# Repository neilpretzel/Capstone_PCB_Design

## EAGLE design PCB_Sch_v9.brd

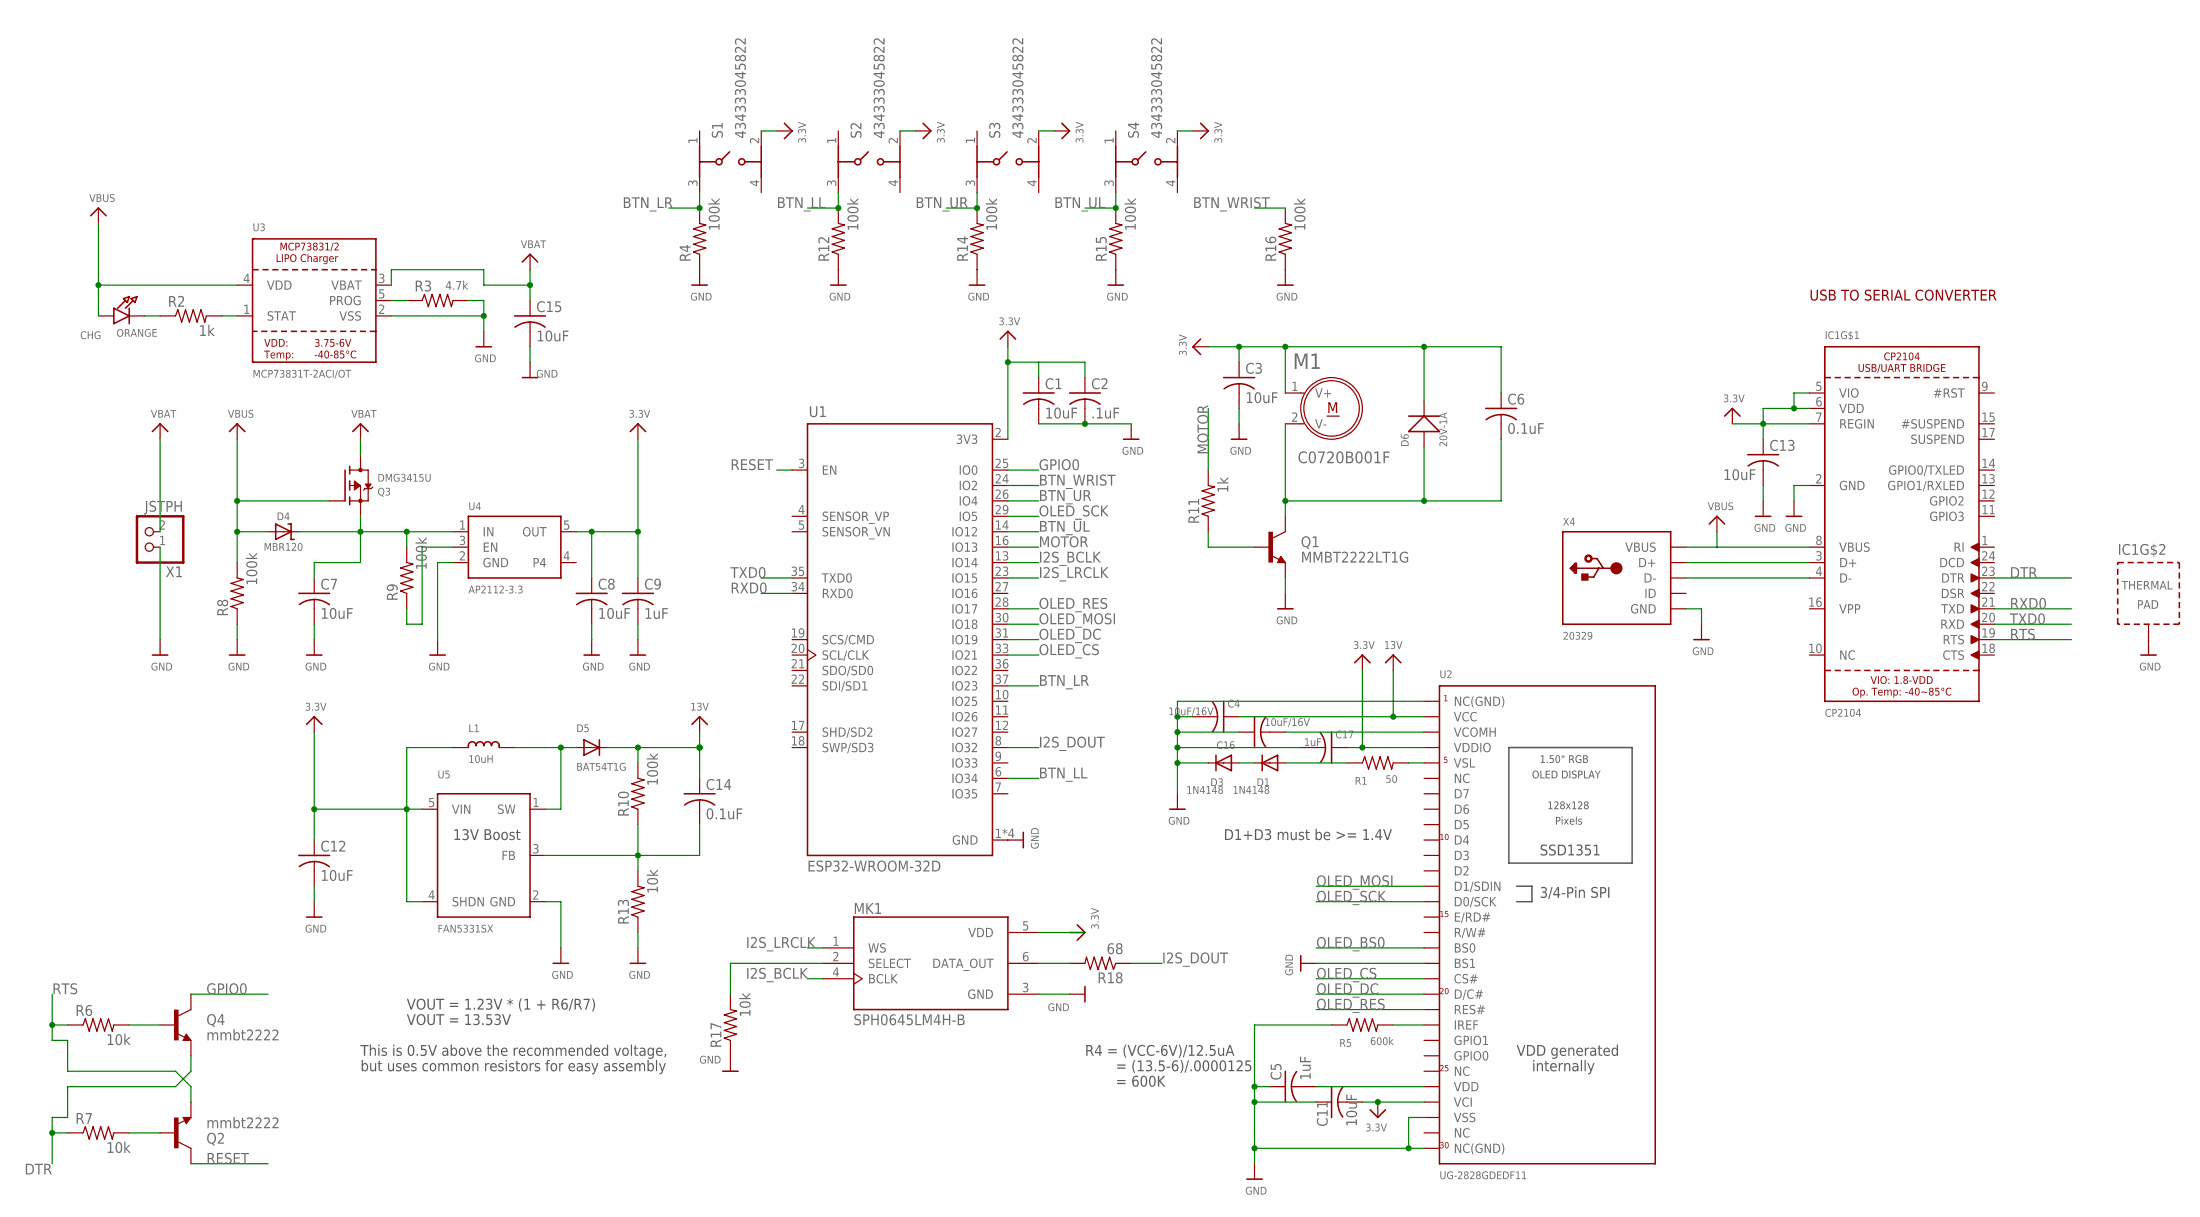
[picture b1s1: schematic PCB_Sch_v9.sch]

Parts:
C1, C3, C7, C8, C11, C12, C13, C15: 10uF; C0603
C2: .1uF; C0603
C4, C16: 10uF/16V; C0603
C5, C9, C17: 1uF; C0603
C6, C14: 0.1uF; C0603
CHG: ORANGE; CHIPLED_0805_NOOUTLINE
D1, D3: 1N4148; SOD-323
D4: MBR120; SOD-123
D5: BAT54T1G; SOD-123
D6: 20V-1A; SOD-123
IC1: CP2104; QFN24_4MM_SMSC
L1: 10uH; INDUCTOR_1007
M1: C0720B001F; XDCR_C0720B001F
MK1: SPH0645LM4H-B; MIC_SPH0645LM4H-B
Q1: MMBT2222LT1G; SOT95P237X111-3N
Q2, Q4: mmbt2222; SOT23-3
Q3: DMG3415U; SOT23-R
R1: 50; R0603
R2, R11: 1k; R0603
R3: 4.7k; R0603
R4, R8, R9, R10, R12, R14, R15, R16: 100k; R0603
R5: 600k; R0603
R6, R7, R13, R17: 10k; R0603
R18: 68; R0603
S1, S2, S3, S4: 434333045822
U1: ESP32-WROOM-32D; MODULE_ESP32-WROOM-32D
U2: UG-2828GDEDF11; FPC_XF2M-3015-1A
U3: MCP73831T-2ACI/OT; SOT23-5
U4: AP2112-3.3; SOT23-5
U5: FAN5331SX; SOT23-5@1
X1: JSTPH; JSTPH2
X4: 20329; 4UCONN_20329_V2

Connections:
3.3V: C1.1, C2.1, C3.1, C6.1, C8.1, C9.1, C11.2, C12.1, C13.1, C17.1, D6.-, IC1.5 (VIO), IC1.6 (VDD), IC1.7 (REGIN), L1.P$1 (1), M1.1 (V+), S1.2 (4), S2.2 (4), S3.2 (4), S4.2 (4), U1.2 (3V3), U2.P$4 (VCI), U2.P$27 (VDDIO), U4.5 (OUT), U5.4 (SHDN), U5.5 (VIN)
13V: C4.1, C14.1, D5.C, R10.2, U2.P$29 (VCC)
BTN_LL: R12.2, S2.3 (1), U1.6 (IO34)
BTN_LR: R4.2, S1.3 (1), U1.37 (IO23)
BTN_UL: R15.2, S4.3 (1), U1.14 (IO12)
BTN_UR: R14.2, S3.3 (1), U1.26 (IO4)
BTN_WRIST: R16.2, U1.24 (IO2)
DTR: IC1.23 (DTR), Q4.2 (E), R7.1
GND: C1.2, C2.2, C3.2, C4.2, C5.1, C7.2, C8.2, C9.2, C11.1, C12.2, C13.2, C15.2, C16.1, C17.2, D3.C, IC1.2 (GND), IC1.THERM (TP), MK1.3 (GND), Q1.2 (E), R3.2, R4.1, R5.1, R8.1, R12.1, R13.1, R14.1, R15.1, R16.1, R17.1, U1.1 (GND), U1.15 (GND), U1.38 (GND), U1.39 (GND), U2.P$1 (NC(GND)), U2.P$3 (VSS), U2.P$13 (BS1), U2.P$30 (NC(GND)), U3.2 (VSS), U4.2 (GND), U5.2 (GND), X1.1, X4.BASE@1 (GND), X4.BASE@2 (GND), X4.GND, X4.SPRT@1 (GND), X4.SPRT@2 (GND), X4.SPRT@3 (GND), X4.SPRT@4 (GND)
GPIO0: Q4.3 (C), U1.25 (IO0)
I2S_BCLK: MK1.4 (BCLK), U1.13 (IO14)
I2S_DOUT: R18.1, U1.8 (IO32)
I2S_LRCLK: MK1.1 (WS), U1.23 (IO15)
MOTOR: R11.2, U1.16 (IO13)
unnamed: IC1.3 (D+), X4.D+
unnamed: Q1.1 (B), R11.1
unnamed: C5.2, U2.P$5 (VDD)
unnamed: MK1.2 (SELECT), R17.2
unnamed: IC1.4 (D-), X4.D-
unnamed: D1.A, R1.1
unnamed: R1.2, U2.P$26 (VSL)
unnamed: Q2.1 (B), R7.2
unnamed: Q4.1 (B), R6.2
unnamed: CHG.C, R2.1
unnamed: D1.C, D3.A
unnamed: C7.1, D4.C, Q3.2 (S), R9.2, U4.1 (IN)
unnamed: D5.A, L1.P$2 (2), U5.1 (SW)
unnamed: R9.1, U4.3 (EN)
unnamed: R2.2, U3.1 (STAT)
unnamed: C14.2, R10.1, R13.2, U5.3 (FB)
unnamed: R3.1, U3.5 (PROG)
unnamed: C16.2, U2.P$28 (VCOMH)
unnamed: R5.2, U2.P$9 (IREF)
unnamed: C6.2, D6.+, M1.2 (V-), Q1.3 (C)
unnamed: MK1.6 (DATA_OUT), R18.2
OLED_BS0: U2.P$14 (BS0)
OLED_CS: U1.33 (IO21), U2.P$12 (CS#)
OLED_DC: U1.31 (IO19), U2.P$11 (D/C#)
OLED_MOSI: U1.30 (IO18), U2.P$18 (D1/SDIN)
OLED_RES: U1.28 (IO17), U2.P$10 (RES#)
OLED_SCK: U1.29 (IO5), U2.P$17 (D0/SCK)
RESET: Q2.3 (C), U1.3 (EN)
RTS: IC1.19 (RTS), Q2.2 (E), R6.1
RXD0: IC1.21 (TXD), U1.34 (RXD0)
TXD0: IC1.20 (RXD), U1.35 (TXD0)
VBAT: C15.1, Q3.3 (D), U3.3 (VBAT), X1.2
VBUS: CHG.A, D4.A, IC1.8 (VBUS), Q3.1 (G), R8.2, U3.4 (VDD), X4.VBUS

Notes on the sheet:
R4 = (VCC-6V)/12.5uA
= (13.5-6)/.0000125
= 600K
D1+D3 must be >= 1.4V
VDD generated
internally
VOUT = 1.23V * (1 + R6/R7)
VOUT = 13.53V
This is 0.5V above the recommended voltage,
but uses common resistors for easy assembly
13V Boost
USB TO SERIAL CONVERTER

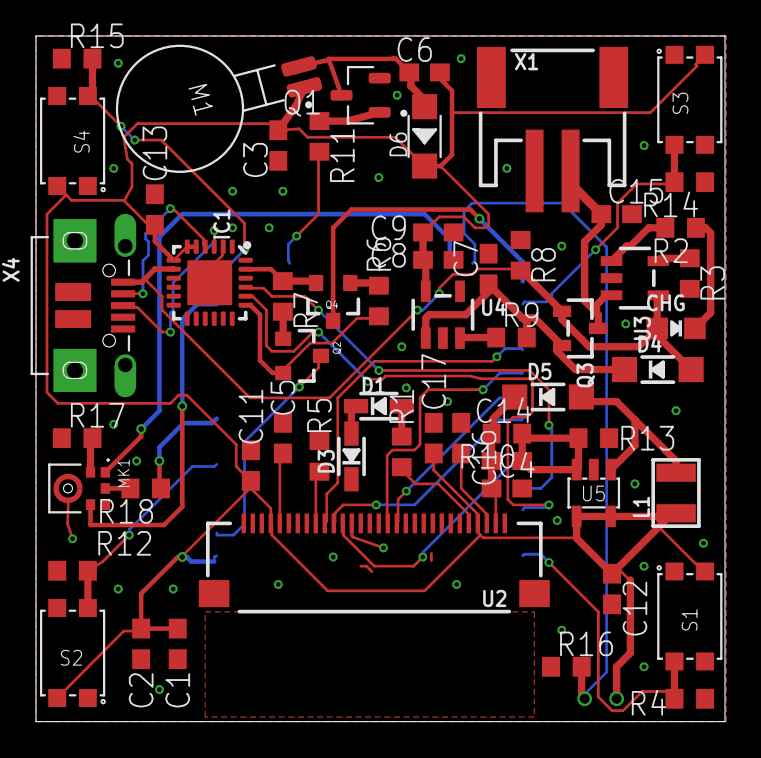
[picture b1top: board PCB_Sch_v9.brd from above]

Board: 2 copper layers, 38.3 x 38.1 mm, 59 parts (1 on the bottom side), 46 nets.

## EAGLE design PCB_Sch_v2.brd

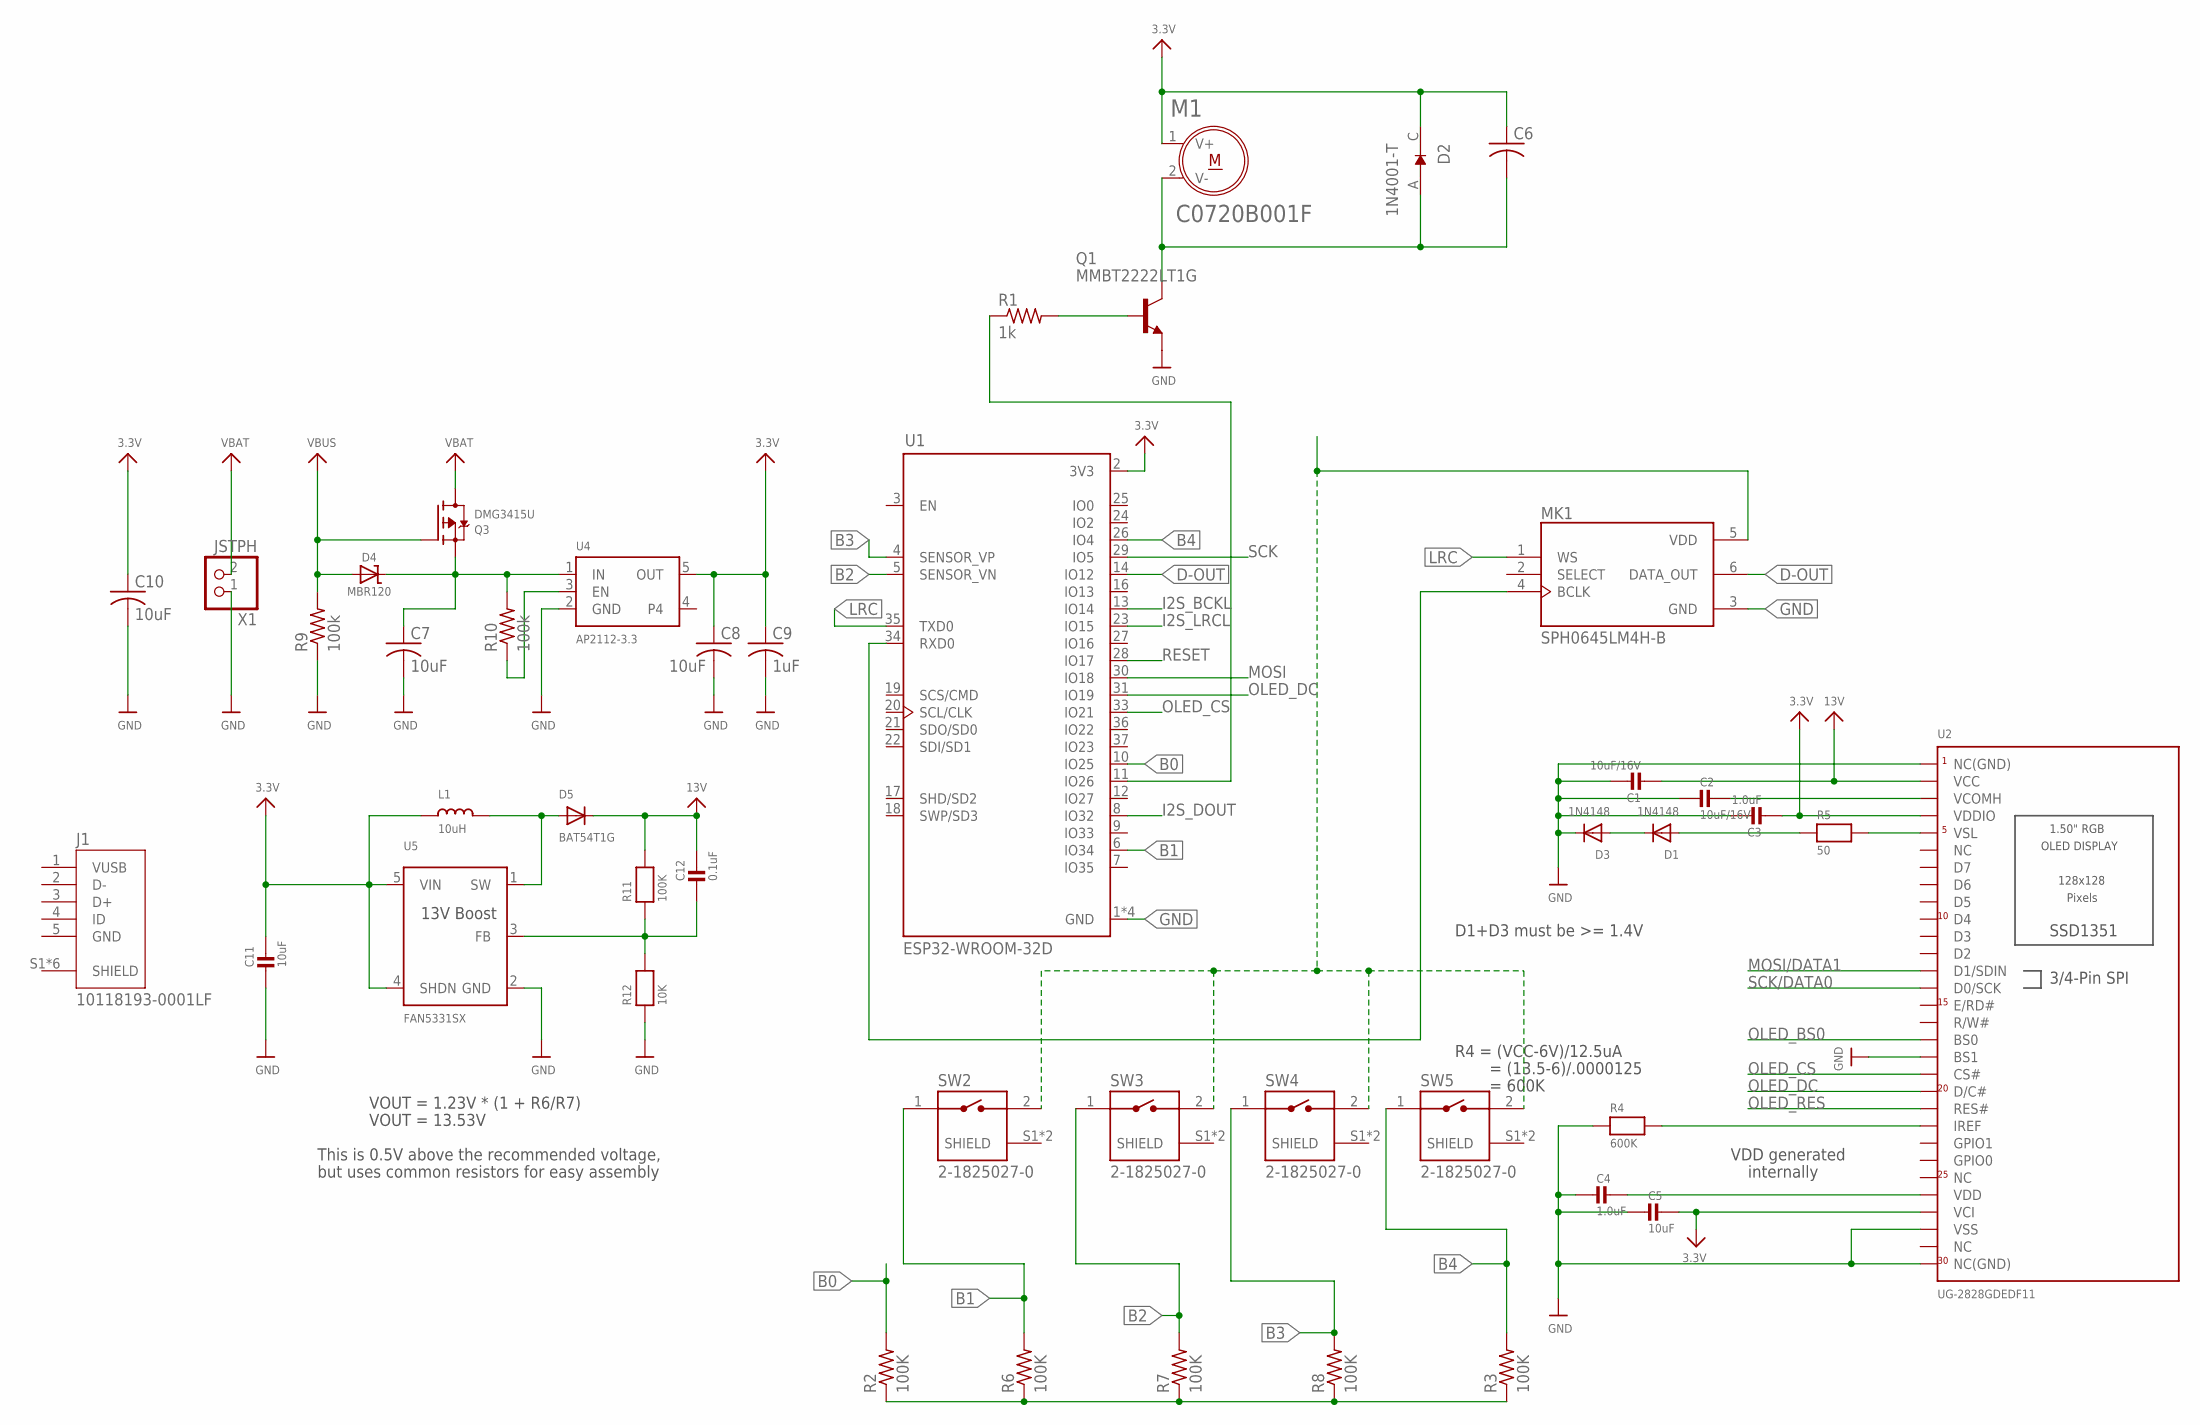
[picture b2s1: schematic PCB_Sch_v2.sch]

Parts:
C1, C2: 10uF/16V; 0805
C3, C4: 1.0uF; 0805
C5, C11: 10uF; 0805
C6: C-USC0805; C0805
C7, C8, C10: 10uF; C0805
C9: 1uF; C0805
C12: 0.1uF; 0805
D1, D3: 1N4148; SOD-323
D2: 1N4001-T; DIOAD953W69L521D272
D4: MBR120; SOD-123
D5: BAT54T1G; SOD-123
J1: 10118193-0001LF; FCI_10118193-0001LF
L1: 10uH; INDUCTOR_1007
M1: C0720B001F; XDCR_C0720B001F
MK1: SPH0645LM4H-B; MIC_SPH0645LM4H-B
Q1: MMBT2222LT1G; SOT95P237X111-3N
Q3: DMG3415U; SOT23-R
R1: 1k; R0805
R2, R3, R6, R7, R8: 100K; R0805
R4: 600K; 0805
R5: 50; 0805
R9, R10: 100k; R0805
R11: 100K; 0805
R12: 10K; 0805
SW2, SW3, SW4, SW5: 2-1825027-0; TE_2-1825027-0
U1: ESP32-WROOM-32D; MODULE_ESP32-WROOM-32D
U2: UG-2828GDEDF11; FPC_XF2M-3015-1A
U4: AP2112-3.3; SOT23-5
U5: FAN5331SX; SOT23-5@1
X1: JSTPH; JSTPH2

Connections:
3.3V: C3.2, C5.1, C6.1, C10.1, C11.1, D2.C, L1.P$1 (1), M1.1 (V+), U1.2 (3V3), U2.P$4 (VCI), U2.P$27 (VDDIO), U5.4 (SHDN), U5.5 (VIN)
13V: C1.2, C12.1, D5.C, R11.2, U2.P$29 (VCC)
B0: R2.2, U1.10 (IO25)
B1: R6.2, SW2.1, U1.6 (IO34)
B2: R7.2, SW3.1, U1.5 (SENSOR_VN)
B3: R8.2, SW4.1, U1.4 (SENSOR_VP)
B4: R3.2, SW5.1, U1.26 (IO4)
D-OUT: MK1.6 (DATA_OUT), U1.14 (IO12)
GND: C1.1, C2.2, C3.1, C4.2, C5.2, C7.2, C8.2, C9.2, C10.2, C11.2, D3.C, MK1.3 (GND), Q1.2 (E), R4.1, R9.1, R12.1, U1.1 (GND), U1.15 (GND), U1.38 (GND), U1.39 (GND), U2.P$1 (NC(GND)), U2.P$3 (VSS), U2.P$13 (BS1), U2.P$30 (NC(GND)), U4.2 (GND), U5.2 (GND), X1.1
I2S_BCKL: U1.13 (IO14)
I2S_DOUT: U1.8 (IO32)
I2S_LRCL: U1.23 (IO15)
IREF: R4.2, U2.P$9 (IREF)
LRC: MK1.1 (WS), U1.35 (TXD0)
MOSI: U1.30 (IO18)
MOSI/DATA1: U2.P$18 (D1/SDIN)
unnamed: Q1.1 (B), R1.2
unnamed: C4.1, U2.P$5 (VDD)
unnamed: C6.2, D2.A, M1.2 (V-), Q1.3 (C)
unnamed: MK1.5 (VDD), SW2.2, SW3.2, SW4.2, SW5.2
unnamed: R5.2, U2.P$26 (VSL)
unnamed: D1.A, R5.1
unnamed: R2.1, R3.1, R6.1, R7.1, R8.1
unnamed: R1.1, U1.11 (IO26)
unnamed: MK1.4 (BCLK), U1.34 (RXD0)
unnamed: D1.C, D3.A
unnamed: C7.1, D4.C, Q3.2 (S), R10.2, U4.1 (IN)
unnamed: D5.A, L1.P$2 (2), U5.1 (SW)
unnamed: R10.1, U4.3 (EN)
unnamed: C12.2, R11.1, R12.2, U5.3 (FB)
OLED_BS0: U2.P$14 (BS0)
OLED_CS: U1.33 (IO21), U2.P$12 (CS#)
OLED_DC: U1.31 (IO19), U2.P$11 (D/C#)
OLED_RES: U2.P$10 (RES#)
OUT: C8.1, C9.1, U4.5 (OUT)
RESET: U1.28 (IO17)
SCK: U1.29 (IO5)
SCK/DATA0: U2.P$17 (D0/SCK)
VBAT: Q3.3 (D), X1.2
VBUS: D4.A, Q3.1 (G), R9.2
VCOMH: C2.1, U2.P$28 (VCOMH)

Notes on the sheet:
R4 = (VCC-6V)/12.5uA
= (13.5-6)/.0000125
= 600K
D1+D3 must be >= 1.4V
VDD generated
internally
VOUT = 1.23V * (1 + R6/R7)
VOUT = 13.53V
This is 0.5V above the recommended voltage,
but uses common resistors for easy assembly
13V Boost

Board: 2 copper layers, 44 parts (0 on the bottom side), 31 nets, no tracks yet.

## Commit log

2019-03-04 Here are some GitHub basics
2019-03-04 Add schematics and images here
2019-03-12 1.44 TFT LCD display
    Eagle pcb folder for 1.44 TFT LCD display, this is just one possible option for display
2019-03-12 ESP32 Feather board
    These are the Eagle files for the ESP32 feather board including all the units
2019-03-12 1.5 OLED display
    These eagle files are for the 1.5 inch OLED display, and this is one of the option for the display
2019-03-12 DRV2605 motor controller
    This folder includes the eagle pcb files for the motor controller of the metronome unit
2019-03-15 added some sch and brd files
2019-03-17 Added libraries and v1
2019-03-17 added more libraries
2019-03-19 Progress made on 03/18/2019
    Connectted excitor and microphone, also contruct some wires for buttons
2019-03-19 Progress made on 3/18/2019
2019-03-20 Added other parts, organized, changed some of the I/O pins
2019-03-25 Added button to libraries, added debouncing caps
2019-03-25 added resistor to microphone
2019-03-25 started board design
2019-03-25 Progress made on 03/25/2019
2019-03-26 All parts are on brd, need to route
2019-03-27 organized board for routing
2019-03-29 Started routing, made some fixes
2019-04-09 Final design

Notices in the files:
parts and their libraries:
SparkFun: Licensing: CC v3.0 Share-Alike You are welcome to use this library for commercial purposes.
